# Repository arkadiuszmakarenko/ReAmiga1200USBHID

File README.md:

RISKYREA1200

## Build Status

Firmware builds are automatically generated for every commit. Pre-built binaries are available in the [GitHub Actions artifacts](https://github.com/arkadiuszmakarenko/RISKYREA1200/actions/workflows/build-firmware.yml).

For detailed information about the build process, see [BUILD.md](BUILD.md).

## About

Mouse Driver
Mouse driver has been provided by sq7bti.

I have used following other projects
- Mist (USB HID parser stack)
- Simon Inns smallymouse2 mouse quadrature encoding
- Amiga Keyboard handler: https://github.com/gianlucarenzi/stalker

This device supports following
- Mouse including scroll functionality (it supports 2 buttons only without a driver)
- Gamepad
- Keyboards

USB supports 4 port Hubs. Only good quality hubs work correctly.

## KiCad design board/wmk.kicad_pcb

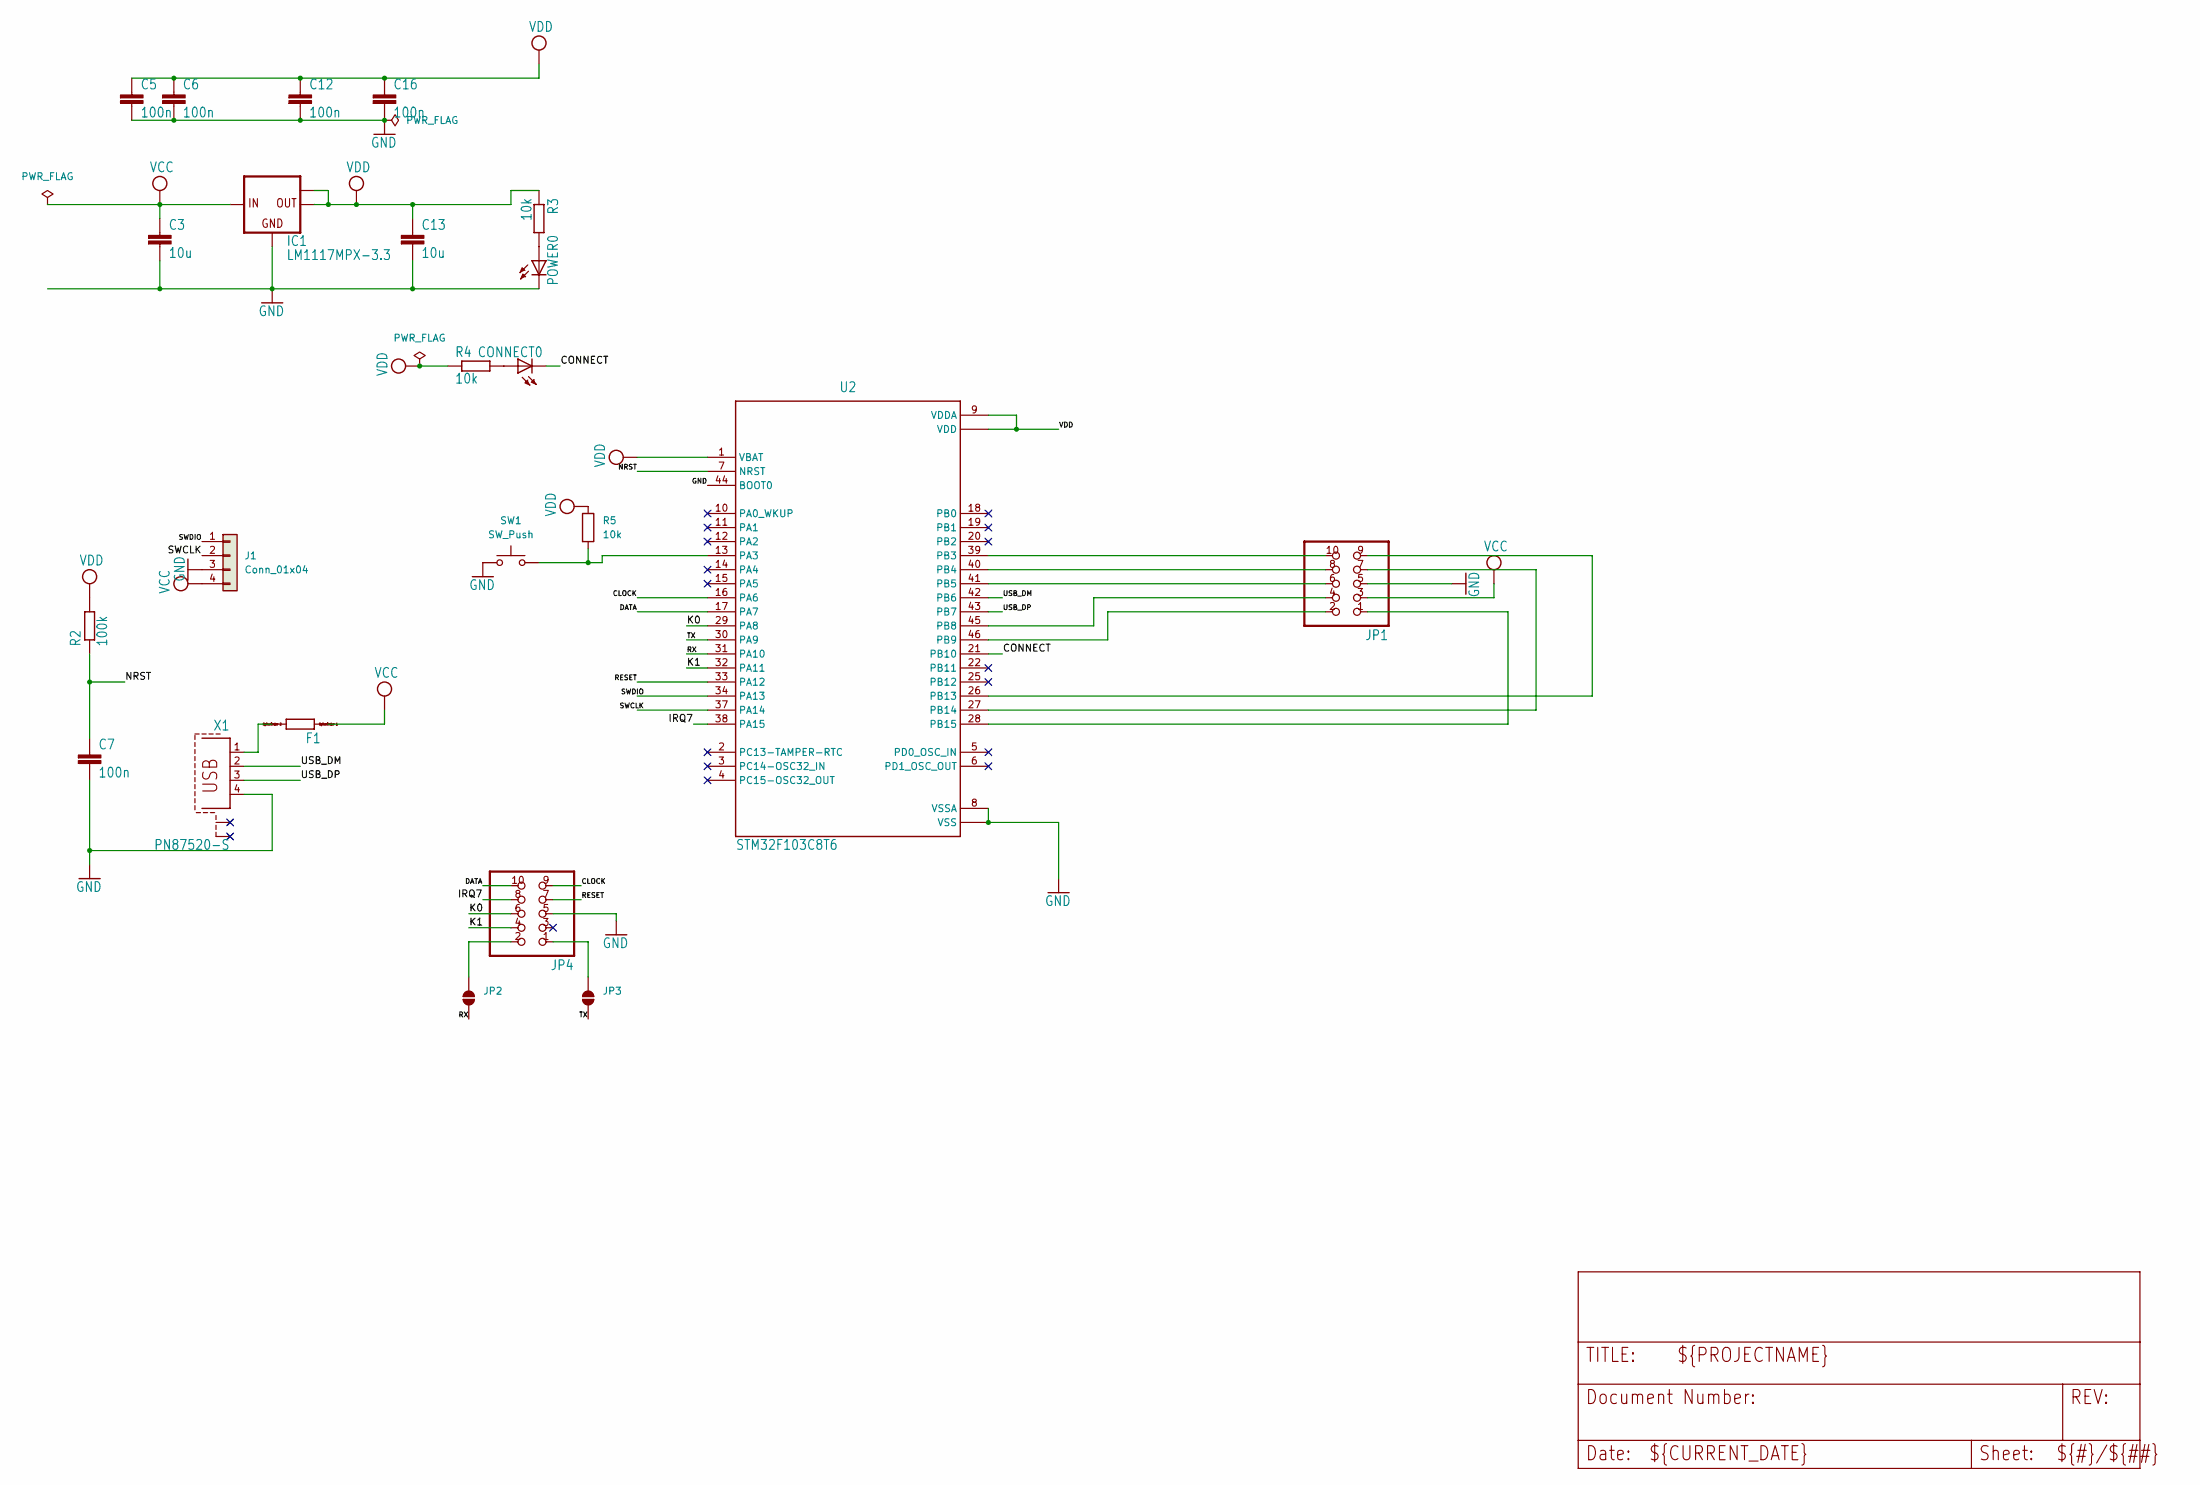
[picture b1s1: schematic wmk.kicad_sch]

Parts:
C3, C13: 10u; C1206
C5, C6, C7, C12, C16: 100n; C0603
CONNECT0: SML0805
F1: R1206
IC1: LM1117MPX-3.3; SOT223
J1: Conn_01x04; PinHeader_1x04_P2.54mm_Vertical
JP1, JP4: PinHeader_2x05_P2.54mm_Vertical
JP2, JP3: SolderJumper_2_Open
POWER0: SML0805
R2: 100k; R0603
R3, R4: 10k; R0603
R5: 10k; R_0603_1608Metric
SW1: SW_Push; SW_PUSH_6mm
U2: STM32F103C8T6; LQFP-48_7x7mm_P0.5mm
X1: PN87520-S

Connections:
/CLOCK: JP4.9, U2.16 (PA6)
/CONNECT: CONNECT0.C, U2.21 (PB10)
/DATA: JP4.10, U2.17 (PA7)
/IRQ7: JP4.8, U2.38 (PA15)
/K0: JP4.6, U2.29 (PA8)
/K1: JP4.4, U2.32 (PA11)
/NRST: C7.1, R2.1, U2.7 (NRST)
/RESET: JP4.7, U2.33 (PA12)
/RX: JP2.1 (A), U2.31 (PA10)
/SWCLK: J1.2, U2.37 (PA14)
/SWDIO: J1.1, U2.34 (PA13)
/TX: JP3.1 (A), U2.30 (PA9)
/USB_DM: U2.42 (PB6), X1.2
/USB_DP: U2.43 (PB7), X1.3
GND: C3.2, C5.2, C6.2, C7.2, C12.2, C13.2, C16.2, IC1.1 (GND), J1.3, JP1.5, JP4.5, POWER0.C, SW1.1, U2.8 (VSSA), U2.23 (VSS), U2.35 (VSS), U2.44 (BOOT0), U2.47 (VSS), X1.4; also elsewhere on the board
unnamed: CONNECT0.A, R4.2
unnamed: F1.2, X1.1
unnamed: JP2.2 (B), JP4.2
unnamed: JP3.2 (B), JP4.1
unnamed: POWER0.A, R3.2
unnamed 20: R5.2, SW1.2, U2.13 (PA3); also elsewhere on the board
unnamed: JP1.10, U2.39 (PB3)
unnamed: JP1.8, U2.40 (PB4)
unnamed: JP1.6, U2.41 (PB5)
unnamed: JP1.4, U2.45 (PB8)
unnamed: JP1.2, U2.46 (PB9)
unnamed: JP1.9, U2.26 (PB13)
unnamed: JP1.7, U2.27 (PB14)
unnamed: JP1.1, U2.28 (PB15)
VCC: C3.1, F1.1, IC1.3 (IN), J1.4, JP1.3
VDD: C5.1, C6.1, C12.1, C13.1, C16.1, IC1.2 (OUT), IC1.TAB (OUT1), R2.2, R3.1, R4.1, R5.1, U2.1 (VBAT), U2.9 (VDDA), U2.24 (VDD), U2.36 (VDD), U2.48 (VDD)

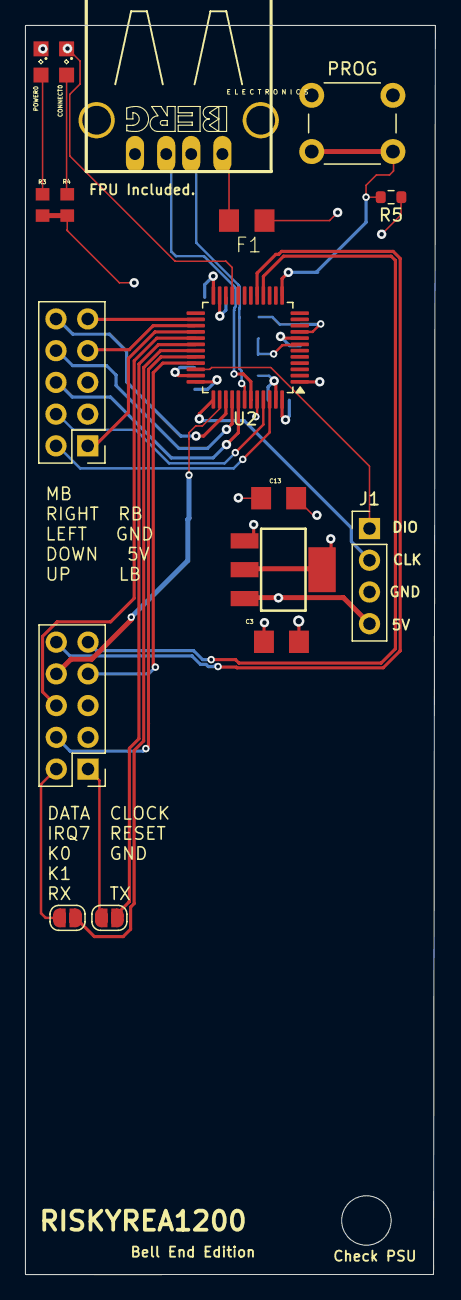
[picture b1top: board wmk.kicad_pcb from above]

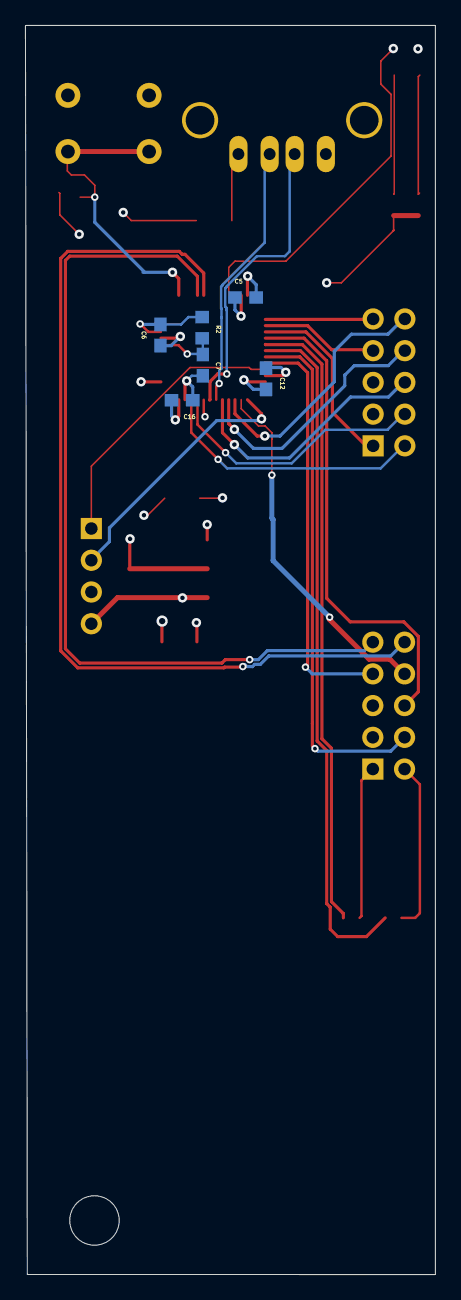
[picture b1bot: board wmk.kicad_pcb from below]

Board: 4 copper layers, 32.8 x 100.0 mm, 23 parts (6 on the bottom side), 31 nets.

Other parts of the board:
PROG: SW_Push; SW_PUSH_6mm

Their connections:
GND: PROG.1; also elsewhere on the board
unnamed 20: PROG.2; also elsewhere on the board

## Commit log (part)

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2024-03-17 Initial release
2024-03-17 remove not needed file
2024-05-11 Board and Firmware
2024-05-11 tidy up
2025-05-05 gerbers
2025-06-10 recompiled with HSI
2025-11-01 initial version
2025-11-01 Tidy up with minimal USB storage working
2025-11-02 Bootloader ready, basic init of app device done.
2025-11-04 makefiles combining bins, debugging sessions.
2025-11-05 remove files
2025-11-05 missing Debug foler in firmare
2025-11-05 Initial plan
2025-11-05 Add GitHub Actions workflow for automated firmware build
2025-11-05 Add comprehensive build documentation and update README
2025-11-05 Update toolchain to WCH RISC-V V2.10 from correct repository
2025-11-05 Add explicit permissions block to workflow for security
2025-11-05 Fix extraction command for RISC-V toolchain
2025-11-05 makefile fix
2025-11-05 Update upload path to include multiple firmware files
2025-11-10 PCB changes and gerbers
2025-12-07 Add K0,K1 and IRQ support. Refactor some functions Tidy up a little
2025-12-07 makefile and project config udpated
2025-12-07 Update comments
2025-12-31 mouse hand fix
2026-01-01 working keyboard code
2026-01-01 refactored code
2026-01-02 makefile update
2026-01-04 Lookup table instead of array
2026-01-04 K0,K1 and IRQ7 support
2026-03-28 Board review
2026-03-28 Update footprint properties for solder jumpers in schematic
